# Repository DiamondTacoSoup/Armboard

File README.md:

# WHY ArmBoard?
We have all been there (well I have at least). Your friend says something funny, goofy, or pretty much anything and you think to yourself "I wish I could play a sound effect IRL, that would inject a lot of humour into this situation". Whether that be a generic laughing track or some obscure in joke, I believe on-demand audio add depth to any situation.

The issue we face as a society is that despite having phones which can play any sound imaginable the process of play a sound on a phone is clunky and time consuming. You must pull out and unlock your phone, look up the audio, find the correct version, wait for it to load, and then finally you can play a sound. The issue here being that this possess is time consuming, and many of these jokes/situations are time dependant.

It is clear from this that the need for a more convenient method of playing audio is required. And what could be more convenient than big buttons strapped to your wrist. It is always within arms reach, literally!  That is why I decided to create the ArmBoard, as an audio solution for the masses.

# How does it work?
The main system is comprised of 3 main parts, the esp32, the screen buttons, and the Dfplayer mini. Each of these systems have multiple sub components and functions. 

The esp32 is the brains of the operations, the TinyPico I have opted to use is optimal due to its small form factor and high number of GPIO pins. Allowing for the control of many differant components within a miniture package.

The screen buttons are made up of two distinct components, the screen and the buttons. The screens I have used are 0.66in two tone OLED displays. These are cheap, small, and bright. I have chosen to use the breakout board version of the screens as it simplifys soldering an circutry. The buttons I have chosen are the cherry MX ultra low profile. Unfortunatly these switches can only be bought from two suppliers, one in china and one in germany, they are also quite pricey. Depsite this I have still used them because of their incredibly thin form factor. 
The TinyPico does not have enough GPIO pins for each switch to have its own, as such I have arrange the switches into 4 sets of 3 switches. Each switch has a differant value resistor attatched to it (1000, 4700, and 10,000 ohm). As such, when pressed each switch in each set will produce a differant voltage. This reduces the number of Inputs needed on the TinyPico from 12 GPIO pins to just 4 analogue inputs. 
The TinyPico communicates to the Displays over I2C. Each display only supports 2 I2C addresses, as such I have had to use an I2C multiplexer to create 6 discrete I2C lines. For this task I have used the TCA9548APWR, a common I2C multiplexer. This takes one I2C line and 3 GPIO pins as input. The I2C lines carry the signal and the GPIO lines select the output using binary where each GPIO represents one digit.

Finally, the sound system consists of a DFplayer mini and a small 0.5w speaker. The DFplayer is a premade mp3 player board, the TinyPico uses a UART connection to select from mp3 files stored on an sd card within the DFplayer. The DFplayer, which incorporates a DAC, amp, and SD card, then outputs that sound signal to the speaker.

# Images
PCB:

Schematic:

3d Models:

# BOM (All prices are AUD)
| PCB designation | Name                               | Quantity | Product number / Website                                                                                                                                                                                                                                  | Unit price | Total price |
|-----------------|------------------------------------|-----------|-------------------------------------------------------------------------------------------------------------------------------------------------------------------------------------------------------------------------------------------------------------|-------------|--------------|
| XA1             | TinyPico                           | 1         | 392-TP-N-01                                                                                                                                                                                                                                                | $30.40      | $30.40       |
| R10,R4,R1,R7    | 3216 Metric 1000Ohm                | 4         | 704-MFBW1V3216-152-R                                                                                                                                                                                                                                      | $0.10       | $0.38        |
| R6,R12,R15,R9,R3,R13,R16,R14 | 3216 Metric 10000Ohm   | 8         | 652-CRT1206BY1002ELF                                                                                                                                                                                                                                      | $0.21       | $1.68        |
| R8,R5,R2,R11    | 3216 Metric 4700Ohm                | 4         | 603-RT1206BRD074K7L                                                                                                                                                                                                                                       | $0.19       | $0.74        |
| U1              | TCA9548APWR                        | 1         | 595-TCA9548APWR                                                                                                                                                                                                                                           | $3.65       | $3.65        |
| U2              | Dfplayer mini                      | 1         | [AliExpress Link](https://www.aliexpress.com/item/1005001417104130.html?src=google&pdp_npi=4%40dis!AUD!3.07!3.07!!!!!%40!12000016020958443!ppc!!!)                                                                                                         | $3.06       | $3.06        |
| SW12,SW3,SW1,SW9,SW2,SW8,SW5,SW10,SW6,SW7,SW11,SW4 | Cherry ULP SMD switches | 12 | [Reichelt Link](https://www.reichelt.de/de/en/shop/product/cherry_mx_ultra_low_profile_rgb_-_pushbutton_module-335040)                                                                                             | $2.66       | $31.92       |
| D8,D4,D2,D12,D6,D10,D7,D3,D5,D9,D11,D1 | Display_0.66in               | 12        | [BuyDisplay Link](https://www.buydisplay.com/i2c-white-0-66-inch-oled-display-module-64x48-arduino-raspberry-pi)                                                                                                   | $4.92       | $59.04       |
| —               | Battery                            | 1         | [AliExpress Link](https://www.aliexpress.com/p/tesla-landing/index.html?scenario=c_ppc_item_bridge&productId=4001029210544&_immersiveMode=true&withMainCard=true&src=google&aff_platform=true&isdl=y)                                                    | $12.39      | $12.39       |
| LS1             | Buzzer_12mm (6.5mm hole)           | 1         | MT-TH12-0126-RK                                                                                                                                                                                                                                           | $2.30       | $2.30        |
| ~               | **Overall cost (excluding shipping)** | ~         | ~                                                                                                                                                                                                                                                         | ~           | **$133.18**  |

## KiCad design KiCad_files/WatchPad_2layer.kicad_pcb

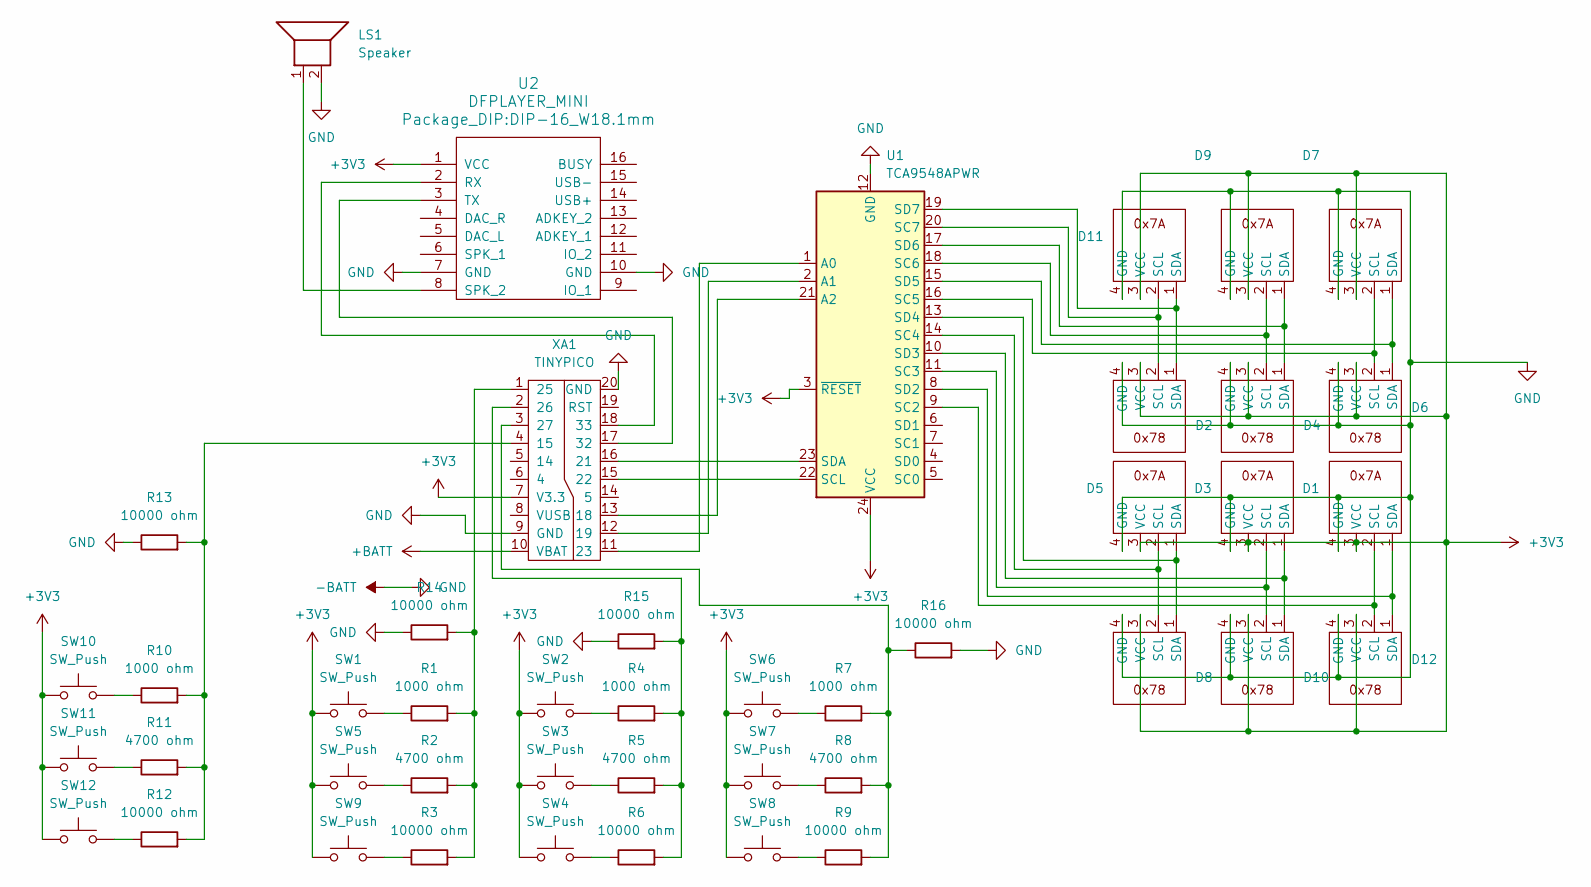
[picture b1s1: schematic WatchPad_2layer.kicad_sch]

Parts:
D1, D3, D5, D7, D9, D11: Display_0.66in_0x7A
D2, D4, D6, D8, D10, D12: Display_0.66in_0x78
LS1: Speaker; Buzzer_TDK_PS1240P02BT_D12.2mm_H6.5mm
R1, R4, R7, R10: 1000 ohm; R_1206_3216Metric
R2, R5, R8, R11: 4700 ohm; R_1206_3216Metric
R3, R6, R9, R12, R13, R14, R15, R16: 10000 ohm; R_1206_3216Metric
SW1, SW2, SW3, SW4, SW5, SW6, SW7, SW8, SW9, SW10, SW11, SW12: SW_Push; Cherry ULP SMD
U1: TCA9548APWR; TSSOP-24_4.4x7.8mm_P0.65mm
U2: DFPLAYER_MINI; DIP-16_W18.1mm
XA1: TINYPICO

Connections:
+3V3: D1.3 (VCC), D2.3 (VCC), D3.3 (VCC), D4.3 (VCC), D5.3 (VCC), D6.3 (VCC), D7.3 (VCC), D8.3 (VCC), D9.3 (VCC), D10.3 (VCC), D11.3 (VCC), D12.3 (VCC), SW1.1, SW2.1, SW3.1, SW4.1, SW5.1, SW6.1, SW7.1, SW8.1, SW9.1, SW10.1, SW11.1, SW12.1, U1.3 (~RESET), U1.24 (VCC), U2.1 (VCC), XA1.7 (V3.3)
+BATT: XA1.10 (VBAT)
-BATT: D1.4 (GND), D2.4 (GND), D3.4 (GND), D4.4 (GND), D5.4 (GND), D6.4 (GND), D7.4 (GND), D8.4 (GND), D9.4 (GND), D10.4 (GND), D11.4 (GND), D12.4 (GND), LS1.2, R13.1, R14.1, R15.1, R16.2, U1.12 (GND), U2.7 (GND), U2.10 (GND), XA1.9 (GND), XA1.20 (GND)
unnamed: D1.2 (SCL), D12.2 (SCL), U1.9 (SC2)
unnamed: D1.1 (SDA), D12.1 (SDA), U1.8 (SD2)
unnamed: D4.2 (SCL), D9.2 (SCL), U1.18 (SC6)
unnamed: D4.1 (SDA), D9.1 (SDA), U1.17 (SD6)
unnamed: D5.2 (SCL), D8.2 (SCL), U1.14 (SC4)
unnamed: D5.1 (SDA), D8.1 (SDA), U1.13 (SD4)
unnamed: D6.2 (SCL), D7.2 (SCL), U1.16 (SC5)
unnamed: D6.1 (SDA), D7.1 (SDA), U1.15 (SD5)
unnamed: D3.2 (SCL), D10.2 (SCL), U1.11 (SC3)
unnamed: D3.1 (SDA), D10.1 (SDA), U1.10 (SD3)
unnamed: D2.2 (SCL), D11.2 (SCL), U1.20 (SC7)
unnamed: D2.1 (SDA), D11.1 (SDA), U1.19 (SD7)
unnamed: R1.1, SW1.2
unnamed: R2.1, SW5.2
unnamed: R3.1, SW9.2
unnamed: R4.1, SW2.2
unnamed: R5.1, SW3.2
unnamed: R6.1, SW4.2
unnamed: R7.1, SW6.2
unnamed: R8.1, SW7.2
unnamed: R9.1, SW8.2
unnamed: R10.1, SW10.2
unnamed: R11.1, SW11.2
unnamed: R12.1, SW12.2
unnamed: U1.1 (A0), XA1.11 (23)
unnamed: U1.2 (A1), XA1.12 (19)
unnamed: U1.21 (A2), XA1.13 (18)
unnamed: U1.22 (SCL), XA1.15 (22)
unnamed: U1.23 (SDA), XA1.16 (21)
unnamed: U2.2 (RX), XA1.18 (33)
unnamed: LS1.1, U2.8 (SPK_2)
unnamed: U2.3 (TX), XA1.17 (32)
unnamed: R10.2, R11.2, R12.2, R13.2, XA1.4 (15)
unnamed: R1.2, R2.2, R3.2, R14.2, XA1.1 (25)
unnamed: R4.2, R5.2, R6.2, R15.2, XA1.2 (26)
unnamed: R7.2, R8.2, R9.2, R16.1, XA1.3 (27)

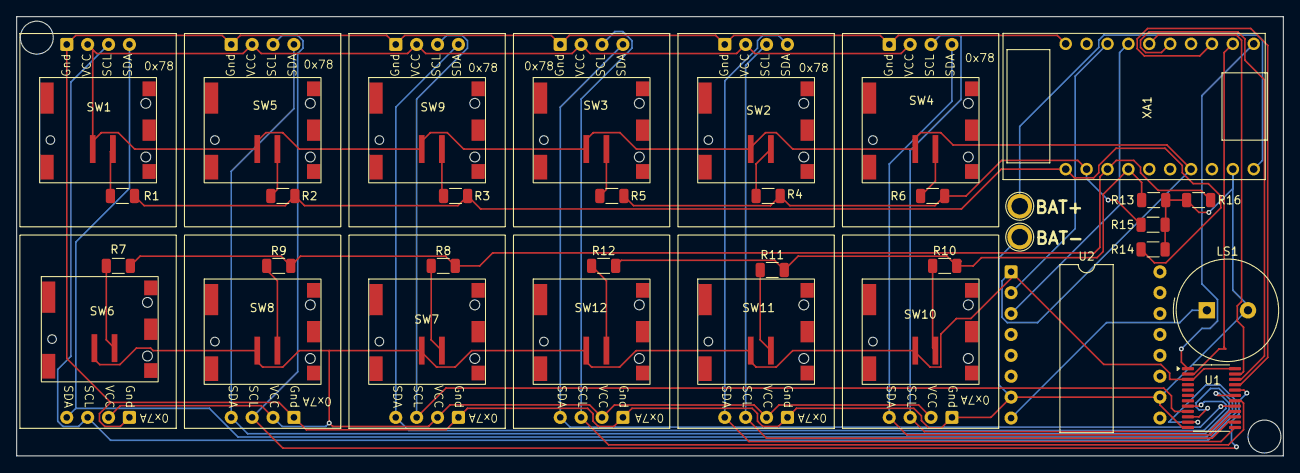
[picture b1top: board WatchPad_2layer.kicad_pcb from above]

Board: 2 copper layers, 154.0 x 53.4 mm, 44 parts (0 on the bottom side), 38 nets.

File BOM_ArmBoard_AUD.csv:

PCB designation,Name,Quantity,Product number/website,Unit price,total price
XA1,TinyPico,1,392-TP-N-01, $30.40 , $30.40 
"R10,R4,R1,R7",3216 Metric 1000Ohm,4,704-MFBW1V3216-152-R, $0.10 , $0.38 
"R6,R12,R15,R9,R3,R13,R16,R14",3216 Metric 10000Ohm,8,652-CRT1206BY1002ELF, $0.21 , $1.68 
"R8,R5,R2,R11",3216 Metric 4700Ohm,4,603-RT1206BRD074K7L, $0.19 , $0.74 
U1,TCA9548APWR,1,595-TCA9548APWR, $3.65 , $3.65 
U2,Dfplayer mini,1,https://www.aliexpress.com/item/1005001417104130.html?src=go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, $3.06 , $3.06 
"SW12,SW3,SW1,SW9,SW2,SW8,SW5,SW10,SW6,SW7,SW11,SW4",Cherry ULP SMD switches,12,https://www.reichelt.de/de/en/shop/product/cherry_mx_ultra_l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, $2.66 , $31.92 
"D8,D4,D2,D12,D6,D10,D7,D3,D5,D9,D11,D1",Display_0.66in,12,https://www.buydisplay.com/i2c-white-0-66-inch-oled-display-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, $4.92 , $59.04 
LS1,Buzzer_12mm (6.5mm hole),1,MT-TH12-0126-RK, $2.30 , $2.30 
~,Overall cost (excluding shipping),~,~, ~ , $133.18

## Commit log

2025-10-04 Added Kicad files
2025-10-04 Added code
2025-10-04 Moved some stuff around in the file system
2025-10-15 Update README.md with Added "how does it work" section
2025-10-28 Added BOM and Slightly changed PCB layout
    Changed mounting solution for speaker to use more standard 6.5mm hole spacing
2025-10-28 added battery to BOM
2025-10-28 Update README.md
    Added images
2025-10-28 Added STEP files
2025-10-28 Changed BOM name to "bom.csv"
2025-10-29 Added .DS_store to .gitignore
    DS_store is a MacOS specific metadata file which has no function for other operating systems.
